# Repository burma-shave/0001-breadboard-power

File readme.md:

Breadboard Power

********************
WARNING: I messed up the dimensions so this will not actually
fit onto a breadboard!
********************

Breadboard power supply created by following along on John Winan's 
"John's Basement" youtube channel:
https://youtube.com/playlist?list=PL3by7evD3F51fKkyrUbH-PCdwPCWc9F8a

John's original design can be found here:
https://github.com/johnwinans/2044-breadboard-power

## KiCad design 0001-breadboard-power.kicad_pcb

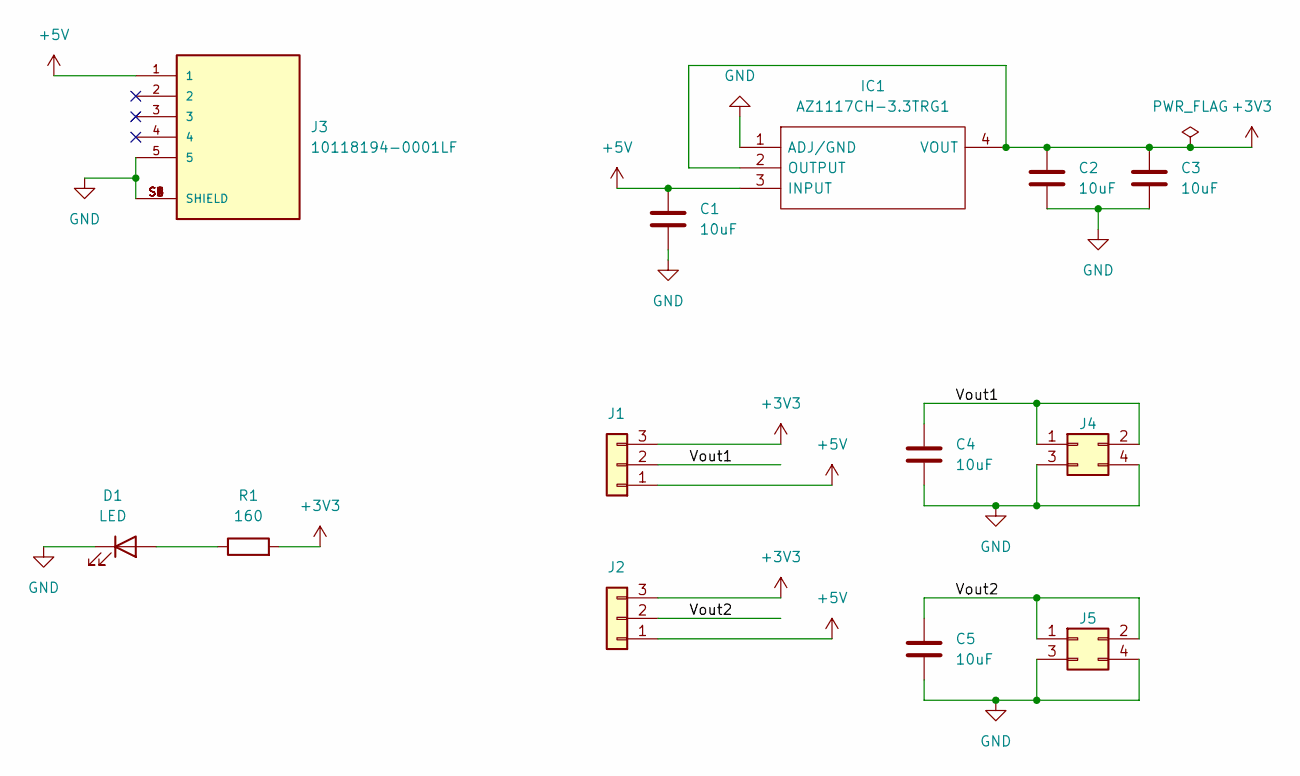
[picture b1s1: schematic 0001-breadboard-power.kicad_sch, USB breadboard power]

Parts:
C1, C2, C3, C4, C5: 10uF; C_0805_2012Metric_Pad1.18x1.45mm_HandSolder
D1: LED; LED_0805_2012Metric_Pad1.15x1.40mm_HandSolder
IC1: AZ1117CH-3.3TRG1; SOT230P700X180-4N; Mouser Part Number 621-AZ1117CH-3.3TRG1
J1, J2: Conn_01x03; PinHeader_1x03_P2.54mm_Vertical
J3: 10118194-0001LF; AMPHENOL_10118194-0001LF; mouser 649-10118194-0001LF
J4, J5: Conn_02x02_Odd_Even; PinHeader_2x02_P2.54mm_Vertical
R1: 160; R_0805_2012Metric_Pad1.20x1.40mm_HandSolder

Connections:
+3V3: C2.1, C3.1, IC1.2 (OUTPUT), IC1.4 (VOUT), J1.3, J2.3, R1.2
+5V: C1.2, IC1.3 (INPUT), J1.1, J2.1, J3.1
/Vout1: C4.1, J1.2, J4.1, J4.2
/Vout2: C5.1, J2.2, J5.1, J5.2
GND: C1.1, C2.2, C3.2, C4.2, C5.2, D1.1 (K), IC1.1 (ADJ/GND), J3.5, J3.S1 (SHIELD), J3.S2 (SHIELD), J3.S3 (SHIELD), J3.S4 (SHIELD), J3.S5 (SHIELD), J3.S6 (SHIELD), J4.3, J4.4, J5.3, J5.4
unnamed: D1.2 (A), R1.1

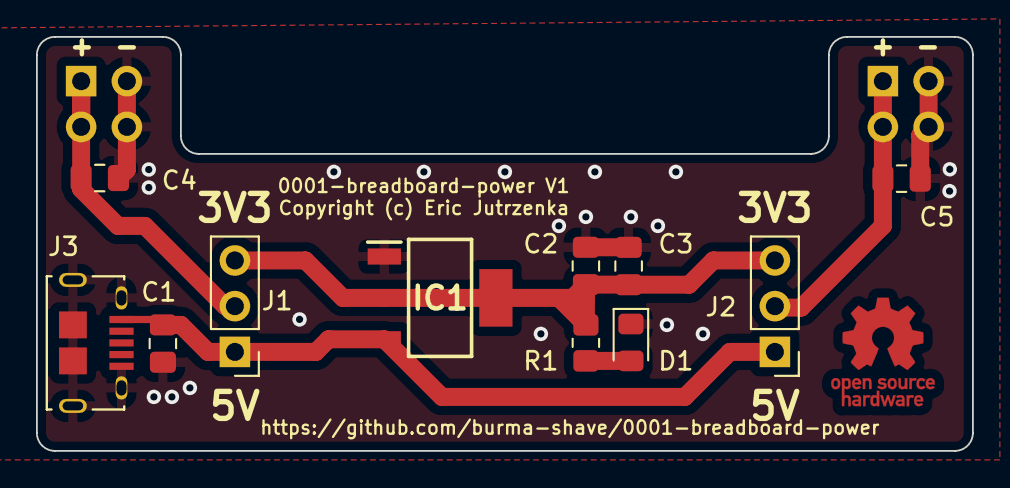
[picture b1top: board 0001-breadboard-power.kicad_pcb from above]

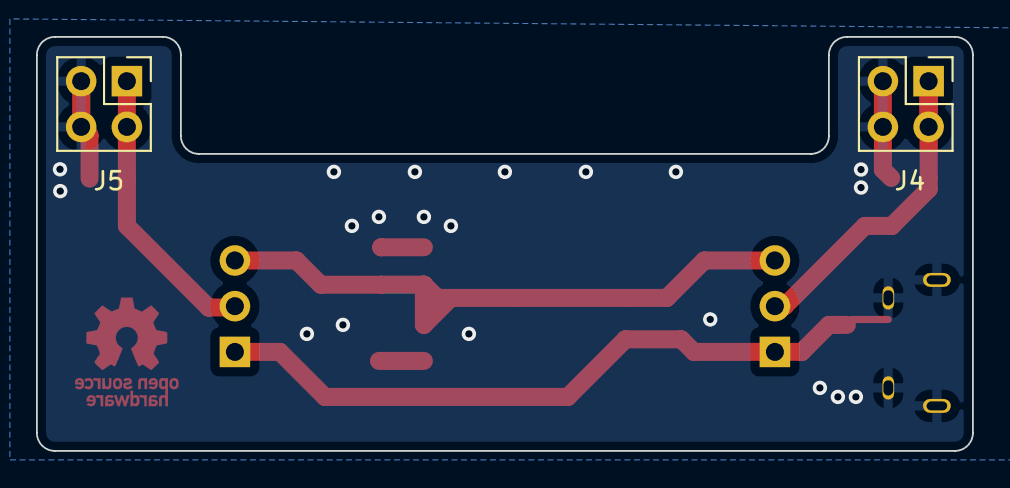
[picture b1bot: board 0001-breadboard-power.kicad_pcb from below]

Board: 2 copper layers, 52.0 x 23.0 mm, 13 parts (2 on the bottom side), 6 nets.

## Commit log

2023-02-07 Fix rotated label

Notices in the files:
0001-breadboard-power.kicad_pcb:
Copyright (c) Eric Jutrzenka
